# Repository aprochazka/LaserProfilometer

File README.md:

# LaserProfilometer - Power Supply

## BP VUT FIT 2022 - Linear Laser Profilometer

#### Power to diode can be adjusted by applying voltage to VSET (0V = 0mA on LASER, 3V = 70mA on LASER) or by sending PWM signal to VSET

#### !! Always have diode connected to LASER connector when applying voltage to VSET or VIN (5V) !!

| Connector   | Max Value   |
| ----------- | ----------- |
| VSET (IN)   | 3V          |
| LASER (OUT) | 70mA        |
| VIN (IN)    | 5V          |

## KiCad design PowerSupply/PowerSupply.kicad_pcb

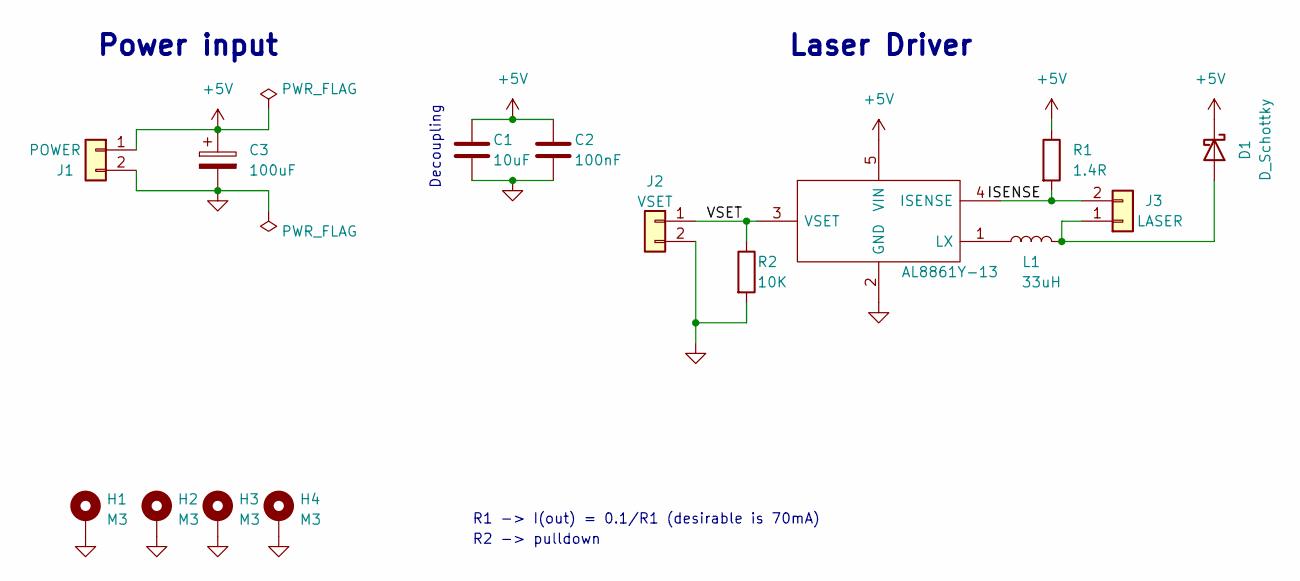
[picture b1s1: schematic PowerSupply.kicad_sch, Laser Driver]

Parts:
C1: 10uF; C_1206_3216Metric_Pad1.33x1.80mm_HandSolder; Manufacturer_Part_Number NOSA106M006R0800; Mouser Part Number 581-NOSA106M006R0800
C2: 100nF; C_1206_3216Metric_Pad1.33x1.80mm_HandSolder; Manufacturer_Part_Number 12066D104KAT4A; Mouser Part Number 581-12066D104KAT4A
C3: 100uF; CP_Elec_5x5.3; Manufacturer_Part_Number 865080142007; Mouser Part Number 710-865080142007
D1: D_Schottky; D_SOD-123F; Manufacturer_Part_Number SL02-GS08; Mouser Part Number 78-SL02
H1, H2, H3, H4: M3; MountingHole_3.2mm_M3_Pad_Via
J1: POWER; Molex_Nano-Fit_105313-xx02_1x02_P2.50mm_Horizontal
J2: VSET; Molex_Nano-Fit_105313-xx02_1x02_P2.50mm_Horizontal
J3: LASER; Molex_Nano-Fit_105313-xx02_1x02_P2.50mm_Horizontal
L1: 33uH; 4800S; Manufacturer_Part_Number 48330SC; Mouser Part Number 580-48330SC
R1: 1.4R; R_1206_3216Metric_Pad1.30x1.75mm_HandSolder; Manufacturer_Part_Number CRCW12061R40FKEAHP; Mouser Part Number 71-CRCW12061R40FKEAH
R2: 10K; R_1206_3216Metric_Pad1.30x1.75mm_HandSolder; Manufacturer_Part_Number CRMA1206AF10M0DKEF; Mouser Part Number 71-CRMA1206AF10M0DKF
U0: AL8861Y-13; SOT-89-5; Mouser Part Number 621-AL8861Y-13

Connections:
+5V: C1.1, C2.1, C3.1, D1.1 (K), J1.1, R1.1, U0.5 (VIN)
/ISENSE: J3.2, R1.2, U0.4 (ISENSE)
/VSET: J2.1, R2.1, U0.3 (VSET)
GND: C1.2, C2.2, C3.2, H1.1, H2.1, H3.1, H4.1, J1.2, J2.2, R2.2, U0.2 (GND)
unnamed: D1.2 (A), J3.1, L1.2
unnamed: L1.1, U0.1 (LX)

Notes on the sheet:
R2 -> pulldown
R1 -> I(out) = 0.1/R1 (desirable is 70mA)
Decoupling
Laser Driver
Power input

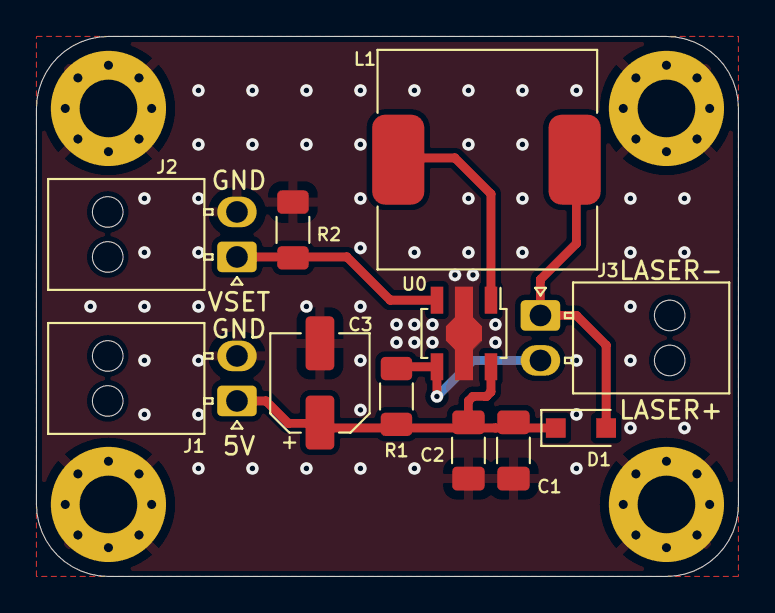
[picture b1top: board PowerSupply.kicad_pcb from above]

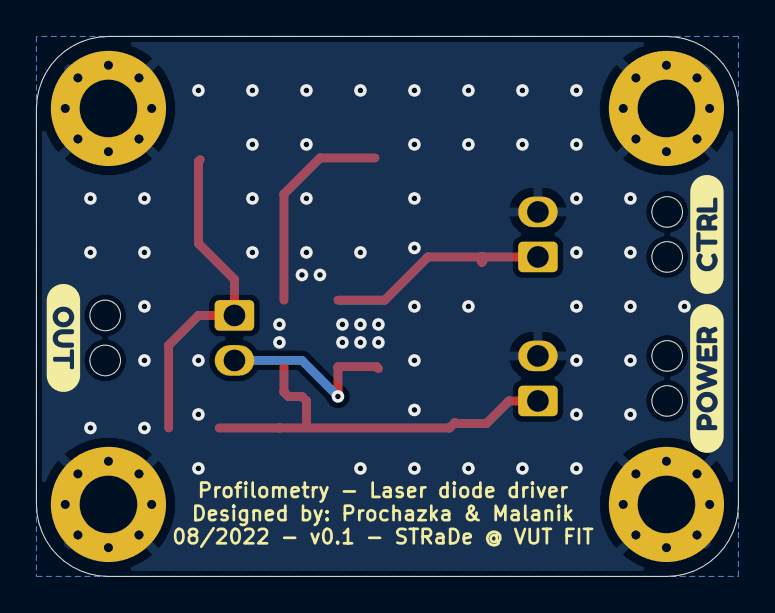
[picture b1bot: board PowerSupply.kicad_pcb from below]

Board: 2 copper layers, 39.0 x 30.0 mm, 18 parts (3 on the bottom side), 6 nets.

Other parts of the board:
kibuzzard-630C9A2E: G***; kibuzzard-630C9A2E
kibuzzard-630C9A4C: G***; kibuzzard-630C9A4C
kibuzzard-630C99F1: G***; kibuzzard-630C99F1

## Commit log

2022-08-02 Add first files
    Filenames are to be changed, need to create folder structure.
2022-08-03 Update folder structure + update power supply sch
2022-08-04 update powersupply
    edit resistor R1 (controling current) value, add pulldown on VSET, add descriptions
2022-08-04 edit footprints
2022-08-12 Add footprints
2022-08-12 Basic pcb layout
2022-08-12 Remove initial commit files
2022-08-15 Review: 1st round - Schema & PCB - General modifications
    All comments in design files, more on chat
2022-08-27 Resolved first review, Routing
2022-08-28 Review: 2st round - PCB - General routing (planes, vias, pads routing)
2022-08-28 Prepare version for manufacturing: finalize PCB layout, add silkscreen
2022-08-29 Resolve comments in second review
2022-08-29 update stitching
2022-08-29 Connection labels
2022-08-29 edit version
2023-02-19 Edit README
